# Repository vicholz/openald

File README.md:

# OpenALD v1.0

**OpenALD** is an open, rechargeable pocket FM radio: an ATmega328PB + RDA5807M (RRD-102 module) board that runs from one
18650 cell, charges and programs over a centred USB-C port, and lives in a 3D-printed 43 × 92 × 33.4 mm case. The repo also
holds an **Adafruit Feather RP2040 variant** built from off-the-shelf boards, and a **6-slot USB-C PD charging dock** that
fits both radios. Everything is KiCad 9 + OpenSCAD, generated by Python scripts.

> **Status: designed, CAD- and datasheet-checked, NOT built and NOT hardware-validated.** ERC/DRC, the JLC placement
> check and the 3D case-fit checks pass, but no board has been built, powered or programmed. The only firmware is the Feather variant's Arduino sketch, which compiles but has never run on hardware; the single board still has none.
> Treat the first build of each part as a prototype (see the bring-up checklist in [HANDOFF.md](HANDOFF.md#8-hardware-bring-up-test-checklist)).

**Picking this up later (person or AI)? Start with [HANDOFF.md](HANDOFF.md)**: full design history, decisions, hard
constraints, open TODOs, test checklist and exact regeneration commands.

| Folder | What it is | Status |
|---|---|---|
| [`radio_single_board/`](radio_single_board/README.md) | **OpenALD v1.0** single-board radio: ATmega328PB + RDA5807M, CH340K USB-C programming, TP4056 ~900 mA charging with DW01A/FS8205A protection and reverse-cell protection, thumbwheel (press = battery check), slide switch, centred vertical 3-LED level bar. 38 × 87 mm 2-layer PCB; case 43 × 92 × 33.4 mm | Designed; ERC/DRC/JLC-CPL/case fit pass; not built |
| [`charging_dock/`](charging_dock/README.md) | **OpenALD Dock v1.0**: 6 radios (2 × 3, 1 in apart) stand USB-C-down in 2 in pockets; one rear USB-C PD input (≥ 45 W charger, 15 V or 20 V); HUSB238 + 2 × SY8205 bucks + SY6280 limit per slot. 192 × 112 × 62.5 mm | Designed; ERC/DRC/JLC-CPL/fit pass; not built |
| [`radio_adafruit_feather_rp2040/`](radio_adafruit_feather_rp2040/README.md) | **OpenALD Feather RP2040 v1.0**: Feather RP2040 + RDA5807M breakout with jack + 18650 holder in a printed frame; **no PCB**: SIQ-02FVS3 wheel glued into a frame cradle, screwless SS-12F16 switch pressed into a groove in the case wall, frame clamped between the case halves, all hand-wired; same dock footprint at the base | Designed; fit check pass; FM-module dimensions are estimates; not built |

Dock ↔ radio mechanical contract: [`charging_dock/DOCK_INTERFACE.md`](charging_dock/DOCK_INTERFACE.md).

## Quick links
* Single-board radio: [Gerbers](radio_single_board/fab/openald-gerbers-jlcpcb.zip) · [JLC BOM](radio_single_board/fab/openald-BOM-jlcpcb.csv) · [JLC CPL](radio_single_board/fab/openald-CPL-jlcpcb.csv) · [human BOM](radio_single_board/fab/openald-BOM-human.csv) · [minimal (4-part) assembly set](radio_single_board/fab/minimal/) · [PCBWay BOM](radio_single_board/fab/openald-BOM-pcbway.xlsx) · [NextPCB BOM](radio_single_board/fab/openald-BOM-nextpcb.xls) · [schematic PDF](radio_single_board/docs/openald-schematic.pdf) · [case STLs](radio_single_board/case/)
* Dock: [Gerbers](charging_dock/fab/openald-dock-gerbers-jlcpcb.zip) · [JLC BOM](charging_dock/fab/openald-dock-BOM-jlcpcb.csv) · [JLC CPL](charging_dock/fab/openald-dock-CPL-jlcpcb.csv) · [human BOM](charging_dock/fab/openald-dock-BOM-human.csv) · [schematic PDF](charging_dock/docs/openald-dock-schematic.pdf) · [case STLs](charging_dock/case/)
* Feather variant: [BOM](radio_adafruit_feather_rp2040/docs/BOM.md) · [pin map](radio_adafruit_feather_rp2040/docs/pin_map.md) · [wiring diagram](radio_adafruit_feather_rp2040/docs/wiring_diagram.png) · [wiring schematic PDF](radio_adafruit_feather_rp2040/docs/wiring_schematic/openald-feather-wiring.pdf) · [firmware](radio_adafruit_feather_rp2040/firmware/) · [firmware notes](radio_adafruit_feather_rp2040/docs/firmware_notes.md) · [case STLs](radio_adafruit_feather_rp2040/case/stl/)
* Ready-made zip packages per subproject: GitHub Release **v1.0** assets (or build them with `tools/make_packages.sh`).

## How to order (JLCPCB)
**Board settings for every board:** 2 layers, **1.6 mm** FR-4, **1 oz** copper, any colour, HASL lead-free (or ENIG),
**PCB Assembly: Economic, top side**. Upload the gerber zip from the subproject's `fab/`, then the `*-BOM-jlcpcb.csv` and
`*-CPL-jlcpcb.csv`. Use the centroid `.csv` or `.pos` only if a site asks for those formats.

* **Check every part's rotation in JLC's placement preview before paying.** The CPLs already contain per-part EasyEDA
  origin/rotation corrections (`JLC_CORR`, verified by `jlc_cpl_fit.py --check`), so the preview should be right; JLC
  engineers sometimes re-rotate by hand.
* Single-board radio: U4 (RRD-102 module), BT1 (18650 holder) and J3 (ISP pads, do not fit) are hand-solder/DNP.
  SW1 (SK-12E12-G5) is THT: choose Standard PCBA to have JLC fit it, or deselect it and hand-solder (5 joints).
  If the ATmega328PB (C132230) is low/out of stock, use **ATmega328P-AU (C14877)**, a drop-in (pick the 328P variant in MiniCore).
* **Minimal assembly option** (you have hot air/hotplate): upload the same gerbers with
  `radio_single_board/fab/minimal/openald-BOM-jlcpcb-minimal.csv` + `openald-CPL-jlcpcb-minimal.csv`. JLC places only
  J1 (USB-C), U1 (TP4056), U3 (ATmega328PB) and U7 (CH340K); buy the rest from LCSC with
  `fab/minimal/openald-LCSC-order-handsolder.csv` (5 boards + labelled spares). Order a separate **frameless** stencil
  (~$3) if you want one for hand paste.
* Dock: the six vertical USB-C plugs J2–J7 (HX TYPE C-M 16P V-SMT, **LCSC C55200592, low stock**) are hand-soldered; buy 7.
* Other vendors (PCBWay/NextPCB) have filled BOM templates, but **the CPL/placement files contain JLC-specific
  corrections**; generate a clean placement file before using another assembler (see HANDOFF §6).
* Cost figures in the docs are **estimates from published price tables (2026-11-10/11)**, not quotes.

## How to regenerate / check
Tested with: **KiCad 9.0.2** (`kicad-cli` + `pcbnew` Python module), **OpenSCAD 2021.01**, **Python 3.13**,
Freerouting (2026-10 build, Java 21+; run with OpenJDK 25) for re-routing only. Python packages: see
[`requirements.txt`](requirements.txt) (`pcbnew` comes with KiCad, not pip).

```bash
pip install -r requirements.txt
tools/fetch_kicad3d.sh && export KICAD9_3DMODEL_DIR=$PWD/tools/kicad3d   # stock KiCad STEP models for the fit checks
tools/check_all.sh            # ERC + DRC + JLC CPL check for all three boards (non-destructive, ~10 s)
tools/check_all.sh --case     # + rebuild cases and run the 3D fit checks (slow; rewrites STLs/previews)
```
Per subproject (details and expected results in [HANDOFF.md §7](HANDOFF.md#7-regeneration-and-checks)):
* `radio_single_board/scripts/run_all_pcb.sh` (full schematic → board → **re-route** → DRC; needs Freerouting),
  `python3 scripts/make_fab.py` / `--minimal`, `python3 scripts/make_vendor_boms.py`, `scripts/build_case.sh`.
* `charging_dock/scripts/run_all_pcb.sh`, `python3 scripts/make_fab.py`, `scripts/build_case.sh`.
* `radio_adafruit_feather_rp2040/make_all.sh` (everything) or `case/build_case.sh` (case only).
* `OPENALD_OFFLINE=1` makes `make_fab.py` reuse the saved `fab/lcsc_lookup.json` prices instead of querying JLC's parts API.
* `FREEROUTING=/path/freerouting.jar` and `JAVA=/path/java` override the router location (default `tools/freerouting.jar`, not in git).
* `EASYEDA_CACHE` overrides the EasyEDA footprint cache used by `jlc_cpl_fit.py` (default: the committed `tools/easyeda/`).

## Directory map
```
README.md            this file            HANDOFF.md        full resume / handoff document
LICENSE              CC0 1.0 Universal    requirements.txt  Python deps
tools/               check_all.sh, fetch_kicad3d.sh, make_packages.sh, easyeda/ (EasyEDA footprint cache for jlc_cpl_fit)
radio_single_board/  kicad/ fab/ (gerbers, JLC BOM/CPL, centroid, .pos, vendor BOMs, minimal/) case/ previews/ docs/ scripts/
charging_dock/       kicad/ fab/ case/ (STLs, floor_pads/) previews/ docs/ scripts/ DOCK_INTERFACE.md
radio_adafruit_feather_rp2040/  case/ (stl/) previews/ docs/ scripts/ ref/ (Adafruit Eagle board, CC BY-SA) archive/ (retired PCB) make_all.sh
```

## License
Released into the public domain under **CC0 1.0 Universal** ([LICENSE](LICENSE)): hardware designs, scripts and docs.
Third-party reference files keep their own licenses (notably the Adafruit Feather RP2040 Eagle file in
`radio_adafruit_feather_rp2040/ref/`, CC BY-SA); see [HANDOFF.md §11](HANDOFF.md#11-license-and-third-party-files).

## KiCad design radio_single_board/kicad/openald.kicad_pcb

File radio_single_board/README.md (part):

# OpenALD: PCB, assembly files and 3D-printed case (v1.0)

OpenALD is an ATmega328PB + RDA5807M (RRD-102 module) FM radio, **programmable over its USB-C port** (CH340K USB-serial, Arduino IDE / MiniCore). It runs from one 18650 cell (reverse-polarity protected), charges over USB-C (TP4056 + DW01A/FS8205A protection) and uses an XC6206 3.3 V LDO. Controls are a thumbwheel encoder with push for volume and tuning (**press the wheel = battery check**; there is no separate battery-check button any more), and a slide power switch that sticks out of the case. A **3-LED battery-level bar** runs as a **vertical column centred across the front face** near the jack end (so it stays well above the rim when the radio stands USB-C-down in the OpenALD Dock), and the TP4056 red/green charge LEDs sit next to the USB-C. The headphone cable acts as the antenna. The board silkscreen reads **OpenALD v1.0**.

> **Note:** I couldn't open the attached spec file on the build machine. This design follows the written summary of the spec instead, so compare it against your original.

> **OpenALD v1.0 is untested hardware.** This release is the former FM radio rev 4.3 design, renamed and reset to v1.0, with no electrical changes. Since then (all still v1.0): the level bar moved to a vertical column near the jack end for the charging dock, and on 2026-11-11 the separate battery-check button SW2 was removed (the wheel press does its job through a small P-FET, Q4) and the bar was centred across the board and moved up (see "Wheel press replaces the battery-check button"). On 2026-11-12 the USB-C receptacle J1 moved 0.9 mm toward the board edge and the case got the Feather's straight cable-plug recess plus assembly notches (see "USB-C 0.9 mm out to the case face"). It passes ERC, DRC and the 3D case-fit check. Pre-release rev 4.2 had two full datasheet reviews, and rev 4.3 (which only changed the charge-current resistor) had its own independent review (see "Pre-release history" below). No board has been built or programmed yet. Build one or two first.

The hardware in this v1.0 package is the ~900 mA charge-current design (R3 = 1.2k, TP4056 PROG). Charge time for a 3000 mAh 18650 is about 3.7 h if the chip holds 900 mA through the CC phase, likely closer to ~4 h in the closed case if the TP4056 thermally throttles. Use a **≥ 1 A charger**. A laptop USB 2.0 port is only rated 500 mA. If you need to charge from a laptop USB-A port, change **R3 to 2.4k (C22940, Basic) for ~460 mA**. See the pre-release rev 4.3 notes for the thermal estimate, USB source details, and the first-board cell-temperature check.

## Board at a glance
| | |
|---|---|
| Size | **38.0 x 87.0 mm**, 1.6 mm FR-4, 2 layers, 1 oz, 3 mm corner radius |
| Mounting | 4x M2 holes (2.2 mm) at (3.2, 3.2), (34.8, 3.2), (3.2, 83.8), (34.8, 83.8) mm from the top-left corner |
| Top side | All SMT parts (including the 3 level-bar LEDs), plus the power switch (THT) and the hand-soldered RRD-102 module |
| Bottom side | MPD BH-18650-PC holder only (THT, hand-soldered) |
| Copper | GND pour on both layers, stitched with 102 GND vias (rev 4.2: 89 stitching vias on two offset 2.5 mm grids, 3 thermal vias in the TP4056 pad, plus routed GND vias). Power nets are 0.5 mm, signals 0.25 mm (0.15 mm minimum at the TQFP/ESSOP pins). Vias are 0.6/0.3 mm (0.8/0.4 mm on power). The autorouter ran with a 0.45 mm edge keep-out |
| ERC | **0 errors**, 2 accepted warnings (`fab/erc_report.txt`): pin_to_pin on U3 pins 3/6 (PE0 tied to GND, PE1 tied to +3V3 for ATmega328P-AU drop-in). This is intentional |
| DRC | **0 errors, 0 unconnected pads, 0 schematic-parity issues** (re-run after the 2026-11-11 wheel-press / centred-bar update). 62 cosmetic silkscreen warnings are waived: 8 silk_edge_clearance (the jack, wheel and switch overhang the edge on purpose), 24 silk_over_copper (reference text over pads/vias) and 30 silk_overlap. Min track 0.187 mm (rule 0.15 mm), tracks/vias ≥ 0.75 mm from the edge (`fab/drc_report.txt`) |

## How charging is shown (power switch off or on)
The power switch cuts VSYS. In rev 4 the MCU also runs from USB with the switch off (see "Power path"), so firmware can show the charging animation on its own while USB is plugged in (optional). The rev 3 options still work:
1. **Always, with no MCU needed:** the TP4056's own LEDs, **D3 red = charging and D4 green = full**, light from USB power. They shine through their own two light tunnels just left of the USB-C. This works with the switch off.
2. **With the switch off, hold the wheel pressed in:** the wheel's push switch turns on P-FET Q4, which powers the MCU from the battery (through D10, and VSYS through D2) for as long as the wheel is held in. While held, the MCU reads nCHRG and shows the charging animation or the level on the bar. Releasing the wheel powers it off again.
3. **With the switch on:** a short press of the wheel any time shows the level on the bar, or the charging animation if USB is charging. Plugging USB in while the radio is on also shows the charging animation once for 3 s.

Rev 4 powers the MCU from USB through its **own** LDO (U6) instead of feeding VBUS into VSYS. That way the FM module and the battery divider stay off. Note that while USB is powering the MCU with the switch off, BAT_ADC reads about 0 V, so the cell voltage isn't measurable then. For the level while charging, hold the wheel in (VSYS then sees the cell through Q4 and D2) or switch on.

## Files
```
kicad/                     KiCad 9 project (open openald.kicad_pro)
  openald.kicad_sch       schematic (PDF in docs/openald-schematic.pdf)
  openald.kicad_pcb       routed board
  openald.pretty/         custom footprints: RRD-102 module, Mitsumi SIQ-02FVS3, HRO SK-12E12-G5 switch (U3/U7/U8 use stock KiCad footprints)
  openald.kicad_sym       custom symbols;  openald.3dshapes/  simple 3D models for previews and the fit check
fab/
  openald-gerbers-jlcpcb.zip   Gerbers + Excellon drill files (upload this)
  openald-BOM-jlcpcb.csv       JLC assembly BOM (Comment, Designator, Footprint, LCSC Part #)
  openald-CPL-jlcpcb.csv       JLC pick-and-place (Designator, Mid X, Mid Y, Layer, Rotation), corrected for EasyEDA origins
  openald-centroid.csv         standard centroid / XY file (Designator, Comment, Footprint, Mid X, Mid Y, Rotation, Layer); same positions as the JLC CPL
  openald.pos                  KiCad ASCII position file (mm); same corrected positions as the centroid/CPL, plus hand-soldered U4 and BT1
  jlc_cpl_fit.json              per-part fit of the EasyEDA footprints (offsets, rotations, pad match)
  openald-BOM-human.csv        full BOM with MPNs, qty, live LCSC stock and price, links, plus hand-solder and off-board parts
  openald-BOM-pcbway.xlsx      PCBWay SMT assembly BOM (official template filled; qty per board; title says 5PCS)
  openald-BOM-nextpcb.xls      NextPCB assembly BOM (official template filled; qty per board)
  minimal/                      JLC files for a 4-part "hotplate" assembly only (see below)
    openald-BOM-jlcpcb-minimal.csv
    openald-CPL-jlcpcb-minimal.csv
    openald-centroid-minimal.csv
    openald-minimal.pos
    openald-LCSC-order-handsolder.csv   remaining LCSC parts for 5 boards, with labelled spares
    cost_estimate.txt
  erc_report.txt, drc_report.txt, lcsc_lookup.json, cost_summary.json
case/
  openald_case.scad       parametric OpenSCAD case (includes case_params.scad)
  case_params.scad         AUTO-GENERATED from the PCB by scripts/gen_case_params.py
  case_top.stl, case_bottom.stl   heat-set-insert version (default)
  nut_variant/             same case with M2 hex-nut pockets instead of inserts
  case_fit_report.txt      3D interference check of the assembled PCB against both halves and the LED tunnel walls
previews/                  pcb_top.png, pcb_bottom.png, pcb_closeup_led_bar.png, pcb_closeup_reverse_polarity.png,
                           pcb_closeup_polarity_marks_bottom.png (rev 4.2), schematic-1.png, case_closed.png, case_*.png,
                           closeup_led_bar.png, closeup_front_usb_leds.png, cutaway_led_tunnels.png (section through the bar),
                           closeup_power_switch.png, closeup_usb_c.png, closeup_thumbwheel.png, closeup_jack_end.png,
                           cpl_overlay_<REF>.png (EasyEDA/JLC footprint vs KiCad pads; rev 4 adds U3/U6/U7/U8, rev 4.2 Q2/Q3, 2026-11-11 Q4),
                           pcb_closeup_usb_serial.png
docs/openald-schematic.pdf
scripts/                   generator scripts. run_all_pcb.sh regenerates everything up to DRC,
                           make_fab.py the fab outputs (add --minimal for the hotplate assembly set),
                           make_vendor_boms.py the PCBWay/NextPCB BOMs (templates in scripts/templates/),
                           build_case.sh the case, its checks and the renders
```

## Ordering at JLCPCB (assembled)
1. Upload `fab/openald-gerbers-jlcpcb.zip`. Settings: 2 layers, 38x87 mm, 1.6 mm, any colour, HASL (lead-free) or ENIG.
2. Turn on **PCB Assembly**, top side.
3. Upload `openald-BOM-jlcpcb.csv` and `openald-CPL-jlcpcb.csv`. If a site asks for a centroid or XY file instead, use `openald-centroid.csv` (same positions, plus value and footprint columns). If it asks for a `.pos` or KiCad position file, use `openald.pos`. U4, BT1 and J3 have no JLC placement, so they show as "not selected". Leave them that way, because you hand-solder them (J3 is not fitted).
4. **SW1 (SK-12E12-G5) is a through-hole part.** If you want JLC to solder it, pick **Standard PCBA**, which adds JLC's THT soldering fee. To keep the cheaper Economic SMT-only service, deselect SW1 and hand-solder it, which is 5 easy joints. Buy it from LCSC (C136720) in that case.
5. **Check every part's orientation in JLC's placement preview** before paying. The CPL has per-part corrections fitted against the EasyEDA footprints JLC uses (see "What changed in rev 3.1"), so the preview should show every part on its pads. The pin-1 and polarity marks to watch are U1, U2, Q1, Q2, Q3, Q4 (SOT-23 FETs), U3 (TQFP-32 pin-1 dot), U5, U6, U7 (CH340K), U8 (USBLC6), D2, D7, D8, D9, D10 and the LEDs D1, D3, D4, D5, D6 (cathode = pad 1, on the left for the bar LEDs). Also check that J1, J2, SW1 and SW3 face the board edge.
6. Parts cost about **$7.32 per board** for the JLC-placed parts (LCSC qty-10 prices from the cached 2026-11-10 lookup, including SW1). The 2026-11-11 wheel-press update removed SW2 (Panasonic EVQ-P7A01P, C79167, Extended, $0.187) and added Q4 (AO3401A, C15127, Basic, $0.081) + R25 (1M, C22935, Basic, $0.002): **−$0.10 per board** vs the previous $7.43, and **one fewer extended part type**. Rev 4.1 was $7.28, **+$0.42 over rev 3.1 ($6.86)**: the ATmega328PB costs more than the ATtiny84A, plus the CH340K ($0.55), the USBLC6 ($0.16), the second XC6206 ($0.13), 3 more B5819W and some passives. On top of that come the PCB, the assembly fee, and the Economic-PCBA extended-part loading fee (~$3.07 per part type per order). There are **11 extended part types**, but **C16581 (TP4056) is a JLC *Preferred* extended part, which has no loading fee**, so **10 types are charged**: C12624, C132230, C136720, C165948, C2830320, C2925423, C351410, C7519, C95562, C968586. That's about **$31 per order** (was ~$34 with SW2; about $28 if you deselect the through-hole SW1 and hand-solder it). Hand-solder and off-board parts add roughly $10 per unit: module ~$1-2, holder ~$3, cell ~$5, screws and inserts.
7. Stock checked 2026-11-10 (re-checked for rev 4.3): **ATmega328PB-AU (C132230) still only 735** (was 2,168 earlier today), R3 1.2k (C22765) 2,137,483 (Basic), AO3401A (C15127) 1,635,833, AO3400A (C20917) 990,950, 1M (C22935) 4,069,811. Earlier check (fallback ATmega328P-AU C14877: 22,013, same footprint and CPL), **CH340K (C968586) 33,016** (CH340N C2977777: 48,107 and CH340C C84681: 97,260 exist, but they are different packages and would need a footprint change), USBLC6-2SC6 (C7519) 28,286, SIQ-02FVS3 1,298, PJ-320D-4A 1,522, SK-12E12-G5 15,527 (EVQ-P7A01P no longer used). Re-check stock before ordering.

## BOM files for PCBWay and NextPCB
`fab/openald-BOM-pcbway.xlsx` and `fab/openald-BOM-nextpcb.xls` are the official vendor templates, filled from the v1.0 human BOM. Quantities are **per board** (75 placements, 37 line items). The PCBWay title says **5PCS** to match a 5-board order; NextPCB has no order-qty field — set the board count on their quote form. U4, BT1 and J3 are marked **DNS** (PCBWay) / **DNP** (NextPCB) so the assembler will not fit them: hand-solder U4 and BT1 yourself, and do not fit a header on J3. SW1 is listed as through-hole (PCBWay Type `thru-hole`). Off-board items (the 18650 cell, M2 screws and inserts) are not in these files; they stay in `openald-BOM-human.csv`. Manufacturer is filled only when the project data names one; most passives, the LEDs, the Schottkys, the beads, U4 and J3 leave that column blank. If you are soldering the boards yourself, buy a few extra 0603 passives and LEDs — quantities were not inflated for spares. Regenerate with `scripts/make_vendor_boms.py`.

## Minimal JLC assembly (hotplate parts only)
If you have a hot-air station and want JLC to place only the parts that are painful by hand, use the files in `fab/minimal/`. Upload the same Gerbers (`fab/openald-gerbers-jlcpcb.zip`), but use:

- `fab/minimal/openald-BOM-jlcpcb-minimal.csv`
- `fab/minimal/openald-CPL-jlcpcb-minimal.csv`

(or the matching centroid / `.pos` if the site asks for those). Regenerated with `python3 scripts/make_fab.py --minimal`. Positions use the same `JLC_CORR` EasyEDA origin/rotation fixes as the full CPL; `jlc_cpl_fit.py --check` and a pad-fit of this 4-row CPL both pass.

**JLC places these four parts (all top side):**

| Ref | Part | Why it is in the minimal set |
|---|---|---|
| J1 | HRO TYPE-C-31-M-12 mid-mount USB-C (C165948) | Mid-mount body sits in board-edge slots; hard to align and easy to melt with an iron or hot air |
| U1 | TP4056 ESOP-8 (C16581) | Exposed pad under the package; needs reflow or a hotplate to solder reliably |
| U3 | ATmega328PB-AU TQFP-32, 0.8 mm pitch (C132230) | No exposed pad, so hot air *can* do it, but 0.8 mm pitch is easy to bridge; factory placement is much more reliable |
| U7 | CH340K ESSOP-10 (C968586) | Exposed pad under the package; same as U1 |

**Looked at, but left off (your hot-air station is enough):** U2 (DW01A, SOT-23-6), Q1 (FS8205A, SOT-23-6 in this design — not TSSOP-8), U8 (USBLC6-2SC6, SOT-23-6), Q2/Q3/Q4 (SOT-23) and U5/U6 (SOT-23-3). All of those have side-only pins and no bottom-only pad. U4, BT1 and J3 stay hand-soldered / unfitted as before.

**Estimated JLC cost for 5 boards (estimate only, not a live quote):** about **$36** before shipping, tax or tariff, using the published Economic PCBA table (setup $8.18, stencil $1.53, $3.07 feeder × 3 extended types, SMT joints, $0.45 confirm-placement) plus ~$2 for 5 bare boards and **$14.35** in parts (qty-1 prices: the 328PB is $1.86 each at qty 5). The TP4056 is a Preferred extended part, so it has no feeder fee. The other three are Extended. Details are in `fab/minimal/cost_estimate.txt`. JLC keeps the Economic stencil; it is not shipped. If you want a stencil for the remaining SMT, order a separate frameless one from JLC (~$3) for hand paste + hot air.

**Parts you buy and solder yourself:** `fab/minimal/openald-LCSC-order-handsolder.csv` is an LCSC order list for everything else on the board that has an LCSC number. Quantities are **5 boards plus labelled spares** (+10 on 0603 passives, +3 on 0603 LEDs and SOD-123 diodes, +2 on 0805/1206 caps, +1 on SOT-23s and unique mechanicals). The Mitsumi wheel (SW3) spare is marked optional because that part is about $3. You also still need the RRD-102 module (U4), the MPD BH-18650-PC holder (BT1), an 18650 cell, and the M2 screws and inserts — those are not in the LCSC list; see the human BOM.

## Hand assembly after JLC delivers the board
| Ref | Part | Notes |
|---|---|---|
| U4 | RRD-102V2.0 RDA5807M module (11x11 mm, 2.0 mm pitch) | Solder flat on its pads, chip side up. Check the L/R pads (see caveats). |
| SW1 | HRO SK-12E12-G5, if JLC didn't fit it | Seat it fully, with the knob pointing off the right edge, and solder the 3 pins and 2 tabs. |
| BT1 | MPD BH-18650-PC holder, bottom side | Polarity is printed on the bottom silk: large "+" / "BAT+" beside the holder at the USB-C end, "−" / "BAT−" at the jack end. **The holder itself can be soldered either way round** (its two pins are symmetric), so fit it with its moulded **+ end (flat contact) on the square pad at the USB-C end** and the spring (−) at the jack end, then check with a meter before inserting a cell. A reversed cell is now harmless (rev 4.2), but the radio won't run until it is turned round. |
| J3 | 2x3 ISP pads | Do not fit a header (the case won't close over it). Use a 2x3 pogo clip/adapter once, to burn the bootloader. |

## Programming
**Once per board, burn the bootloader over ISP:**
1. Arduino IDE -> Boards Manager: install **MiniCore** (MCUdude; board-manager URL `https://mcudude.github.io/MiniCore/package_MCUdude_MiniCore_index.json`).
2. Tools: Board **ATmega328**, Variant **328PB** (or **328P / 328PA** if you fitted the C14877 fallback), Clock **Internal 8 MHz**, BOD **2.7 V** (or 1.8 V), EEPROM retained, Bootloader **Yes (UART0)**, Baud rate: the default (38400 for 8 MHz internal is the safest; 115200 is often unreliable on the RC oscillator).
3. Connect a **3.3 V** ISP programmer (USBasp set to 3.3 V, or an Arduino-as-ISP with a level-safe setup) to the J3 pogo pads (standard 6-pin AVR ISP, pin 1 = MISO). Either let the programmer supply 3.3 V on VCC, or set it to "no power" and power the board from USB-C with the switch off. **Never put 5 V on VCC.** It would back-feed the RDA5807M through the I2C lines and push 5 V into U6's output.
4. Tools -> **Burn Bootloader**. This sets the fuses (internal 8 MHz) and writes Optiboot.

**After that, upload over USB-C:** plug in USB-C (the power switch can stay **off**, and the radio stays unpowered), choose the CH340 serial port, and click **Upload** with the same MiniCore settings. DTR# auto-resets the MCU into Optiboot. Windows needs the WCH CH340/CH341 driver (CH341SER), and macOS 11+ / Linux include one.

**Power switch:** slide toward the headphone-jack end = **ON**; toward the USB-C end = OFF. On an SPDT slide switch, the slider joins the common pin (2) to the outer pin on the knob's side, so the knob at the pin-3 end connects 2-3. Pin 2 is VBAT and pin 3 is VSYS, so 2-3 = ON. Pin 3 is the pin nearest the jack end. Check with a meter before closing the case.

## ATmega328PB pin map (TQFP-32) - MiniCore Arduino pin names
| Pin | Port | Arduino | Net | Function |
|---|---|---|---|---|
| 1 | PD3 / INT1 | D3 | ENC_B | encoder B (internal pull-up) |
| 2 | PD4 | D4 | - | **spare** since 2026-11-11 (was ENC_SW). The wheel press is now read on PC1 / BTN_SENSE (pin 24) |
| 3 | PE0 | (D23) | GND | tied to GND for ATmega328P drop-in. **Leave as input, no pull-up** |
| 4 | VCC | | +3V3 | MCU rail (U6), 100 nF C7 |
| 5 | GND | | GND | |
| 6 | PE1 | (D24) | +3V3 | tied to +3V3 for ATmega328P drop-in. **Leave as input, no pull-up** |
| 7, 8 | PB6, PB7 | | - | no crystal (internal 8 MHz RC); spare |
| 9 | PD5 / OC0B | D5 | LVL1 | level LED 1 (D1, bottom of the column / lowest), 1k, active high, PWM |
| 10 | PD6 / OC0A | D6 | LVL2 | level LED 2 (D5, middle), 1k, active high, PWM |
| 11, 12 | PD7, PB0 | D7, D8 | - | spare |
| 13 | PB1 / OC1A | D9 | LVL3 | level LED 3 (D6, top of the column, nearest the jack / full), 1k, active high, PWM |
| 14 | PB2 | D10 | - | spare |
| 15 | PB3 / MOSI | D11 | MOSI | ISP only (J3) |
| 16 | PB4 / MISO | D12 | MISO | ISP only (J3) |
| 17 | PB5 / SCK | D13 | SCK | ISP only (J3) |
| 18 | AVCC | | +3V3 | 100 nF C13 |
| 19 | ADC6 | A6 | - | spare (analog only) |
| 20 | AREF | | AREF | 100 nF C14 (use the internal 1.1 V reference) |
| 21 | GND | | GND | |
| 22 | ADC7 | A7 | - | spare (analog only) |
| 23 | PC0 / ADC0 | A0 | BAT_ADC | battery voltage (VSYS), 47k/12k divider + 100 nF (rev 4.1) |
| 24 | PC1 / ADC1 | A1 | BTN_SENSE | **wheel press** (SW3 S → Q4 → VBTN → 4.7k/10k divider; **high = pressed**, no pull-up: `pinMode(A1, INPUT)`; can also be read as ADC1, threshold ≈ 1.3 V). Wakes the MCU via PCINT9 |
| 25 | PC2 | A2 | CHRG_SENSE | TP4056 nCHRG through Schottky D7; enable the internal pull-up; **low = charging** |
| 26 | PC3 | A3 | - | spare |
| 27 | PC4 / SDA0 | A4 (SDA) | SDA | I2C to RDA5807M (1k series R16, 4.7k pull-up R14 to +3V3R) |
| 28 | PC5 / SCL0 | A5 (SCL) | SCL | I2C (1k series R17, 4.7k pull-up R15 to +3V3R) |
| 29 | PC6 / RESET | | nRESET | 10k pull-up R10, ISP RESET, DTR# auto-reset via 100 nF C19 |
| 30 | PD0 / RXD0 | D0 | MCU_RX | from CH340K TXD (10k pull-up R19) |
| 31 | PD1 / TXD0 | D1 | MCU_TX | to CH340K RXD through 1k R20 |
| 32 | PD2 / INT0 | D2 | ENC_A | encoder A (internal pull-up) |

**Pin budget:** 16 I/O are used, and PB0, PB2, PB6, PB7, PC3, PD4, PD7 and ADC6/7 are spare (not broken out). nSTDBY (full) isn't read: "full" is the same as "USB present, not charging, cell ≥ 4.10 V". The green D4 shows "full" in hardware.

Firmware notes: use the hardware TWI (`Wire`). The RDA5807M uses I2C address 0x10 for sequential access and 0x11 for random access. Before talking to the radio, check that it is powered (switch on), because with only USB present the +3V3R rail and the I2C pull-ups are off. Measure BAT_ADC against the internal 1.1 V reference (`analogReference(INTERNAL)`): V_sys = ADC/1023 x 1.1 x 59/12 (rev 4.1 divider 47k/12k). With these values 4.2 V reads about 0.85 V (ADC ≈ 795 with a nominal 1.1 V reference); calibrate the reference once per board, since it is only guaranteed 1.0-1.2 V. **Don't call `Wire.begin()` while the radio rail is off** (switch off): it enables the AVR's internal pull-ups on SDA/SCL, which would trickle ~80 µA per line into the unpowered RDA5807M; start `Wire` only after V_sys > 3 V, and call `Wire.end()` plus `pinMode(SDA/SCL, INPUT)` before the radio loses power. Keep BOD at 2.7 V (8 MHz needs ≥ ~2.4 V). If you only need it for programming, call `Serial.end()` and leave PD1 as an input when you don't need serial.

### Firmware spec: thumbwheel encoder (SIQ-02FVS3)

Paper-verified against the Mitsumi SIQ series datasheet ([LCSC copy of the official PDF](https://datasheet.lcsc.com/datasheet/pdf/7bff72617d5a3503f5ed21ab02a77dea.pdf?productCode=C2925423)). Nothing here has been tested on hardware.

The part is a 15-detent quadrature encoder plus a momentary slide/push switch. Terminals A and B are the encoder contacts, S is the push switch, and C is the common for all three (see the datasheet "CIRCUIT" diagram). On this board C is tied to GND, A goes to **D2 / PD2 / INT0** and B to **D3 / PD3 / INT1**. **The push switch S no longer goes to an MCU pin** (2026-11-11, it replaced the battery-check button): S drives the gate of P-FET **Q4** (AO3401A) with a 1 MΩ pull-up R25 to VBAT. Pressing the wheel pulls the gate to GND, Q4 switches VBAT onto VBTN, and the MCU sees the press as **BTN_SENSE high on A1 / PC1** (4.7k/10k divider; no internal pull-up). The same path powers the MCU when the power switch is off, so holding the wheel in is the off-state battery check. The S contact carries only ~4 µA (VBAT / 1 MΩ). A and B have no external pull-ups, no RC filters and no ESD diodes: enable the ATmega328PB internal pull-ups (20–50 kΩ, DS40001906) in `setup()` with `INPUT_PULLUP`. At 3.3 V that is about 66–165 µA per closed contact, under the 0.5 mA / 5 V DC rating. The datasheet does not specify a minimum wetting current or a bounce time.

The output is a 2-bit Gray-code quadrature waveform, **one full cycle (four valid state changes) per detent** (24° ±3°, 15 detents per turn). Clockwise, A leads B. At rest in a detent, A and/or B may already be low, so do **not** use INT0/INT1 low-level interrupts to wake from Power-down — the MCU would never stay asleep. Pin-change interrupts on PD2/PD3 (`PCINT18/19`, PCI2) for the turn and on PC1 (`PCINT9`, PCI1) for the press do wake from Power-down and Standby on any edge (BTN_SENSE idles low and goes high on a press). INT0/INT1 any-edge interrupts are fine while awake, but a 1 ms poll of the state table below also debounces, so a timer tick is the simplest approach. Count **one step per detent** (accumulate ±4 transitions), not one step per edge, or volume will jump four units per click.

**Wheel behaviour (v1.0, 2026-11-11):**

| Action | Power switch ON | Power switch OFF |
|---|---|---|
| Turn | volume | nothing (MCU unpowered, or on USB only) |
| **Short press** (released < 500 ms, no turn while pressed) | **battery check**: bar shows the level (or the charging animation) for 3 s | — |
| **Hold pressed** | after 500 ms with no turn: **seek** (next station) | **battery check while held**: the press itself powers the MCU; bar shows level / charging until release |
| Push and turn | tune (step the frequency); no battery check, no seek | — |

The switch-off case is detected at power-on: a power-on reset with BTN_SENSE already high means "wheel-powered" (see the battery-bar spec). There is no mute function on the wheel (there never was one); add one in firmware if you want it, e.g. double-press.

Example (MiniCore, board "ATmega328PB", 8 MHz internal). Call `encoder_setup()` from `setup()`, and `encoder_poll()` from a 1 ms tick or from `loop()` if you wait on `millis()`.

```cpp
// D2=ENC_A (PD2/INT0), D3=ENC_B (PD3/INT1), A1=BTN_SENSE (PC1): wheel press, HIGH = pressed
// (SW3 S -> Q4 gate; Q4 -> VBTN -> 4.7k/10k divider). Common C = GND. D4 (PD4) is spare.
const uint8_t PIN_A = 2, PIN_B = 3, PIN_SW = A1;
// prev<<2|curr -> +1 / -1 for a valid 1-step Gray-code move; 0 = bounce or invalid
static const int8_t ENC_TAB[16] = {
  0,-1,+1,0, +1,0,0,-1, -1,0,0,+1, 0,+1,-1,0
};
static uint8_t enc_prev;
static int8_t  enc_accum;
static int8_t  enc_step;        // +1 / -1 once per detent; consume in the main loop
static uint8_t sw_hist, sw_down, sw_turned;
static uint16_t sw_ms;
volatile uint8_t battery_check_request, seek_request;   // consumed by the main loop

void encoder_setup() {
  pinMode(PIN_A, INPUT_PULLUP);
  pinMode(PIN_B, INPUT_PULLUP);
  pinMode(PIN_SW, INPUT);         // external 10k pull-down R7; do NOT enable the pull-up
  enc_prev = (digitalRead(PIN_A) ? 2 : 0) | (digitalRead(PIN_B) ? 1 : 0);
}

void encoder_poll() {            // call every 1 ms
  uint8_t now = (digitalRead(PIN_A) ? 2 : 0) | (digitalRead(PIN_B) ? 1 : 0);
  enc_accum += ENC_TAB[(enc_prev << 2) | now];
  enc_prev = now;
  if (enc_accum >= 4)  { enc_step += 1; enc_accum = 0; }
  if (enc_accum <= -4) { enc_step -= 1; enc_accum = 0; }

  sw_hist = (sw_hist << 1) | (digitalRead(PIN_SW) ? 0 : 1);   // 0 = pressed (BTN_SENSE high)
  if (!sw_down && (sw_hist & 0x1F) == 0x00) { sw_down = 1; sw_ms = 0; sw_turned = 0; }  // 5 ms pressed
  if (sw_down) {
    if (enc_step) sw_turned = 1;            // push-and-turn = tune (main loop reads enc_step + sw_down)
    if (sw_ms < 60000) sw_ms++;
    if ((sw_hist & 0x1F) == 0x1F) {         // released
      if (sw_ms < 500 && !sw_turned) battery_check_request = 1;   // short press: show the bar for 3 s
      sw_down = 0;
    } else if (sw_ms == 500 && !sw_turned) {
      seek_request = 1;                     // long press: start seek
    }
  }
}
```

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
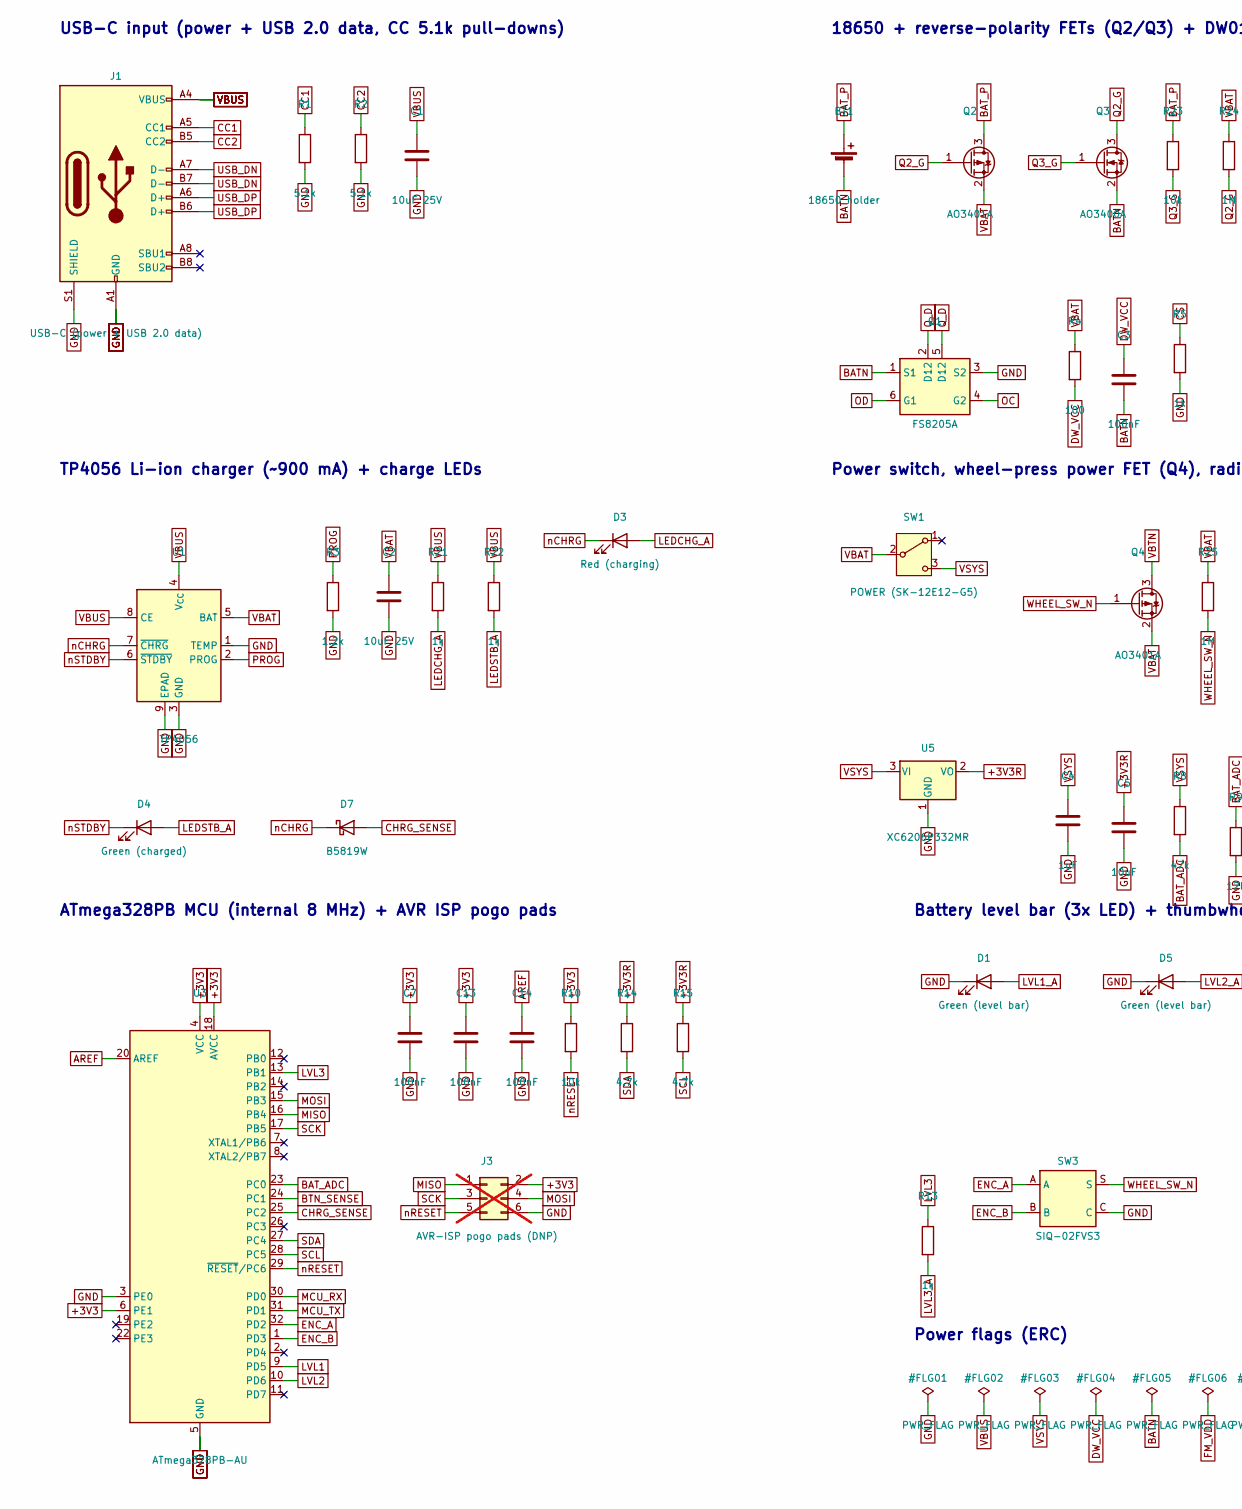
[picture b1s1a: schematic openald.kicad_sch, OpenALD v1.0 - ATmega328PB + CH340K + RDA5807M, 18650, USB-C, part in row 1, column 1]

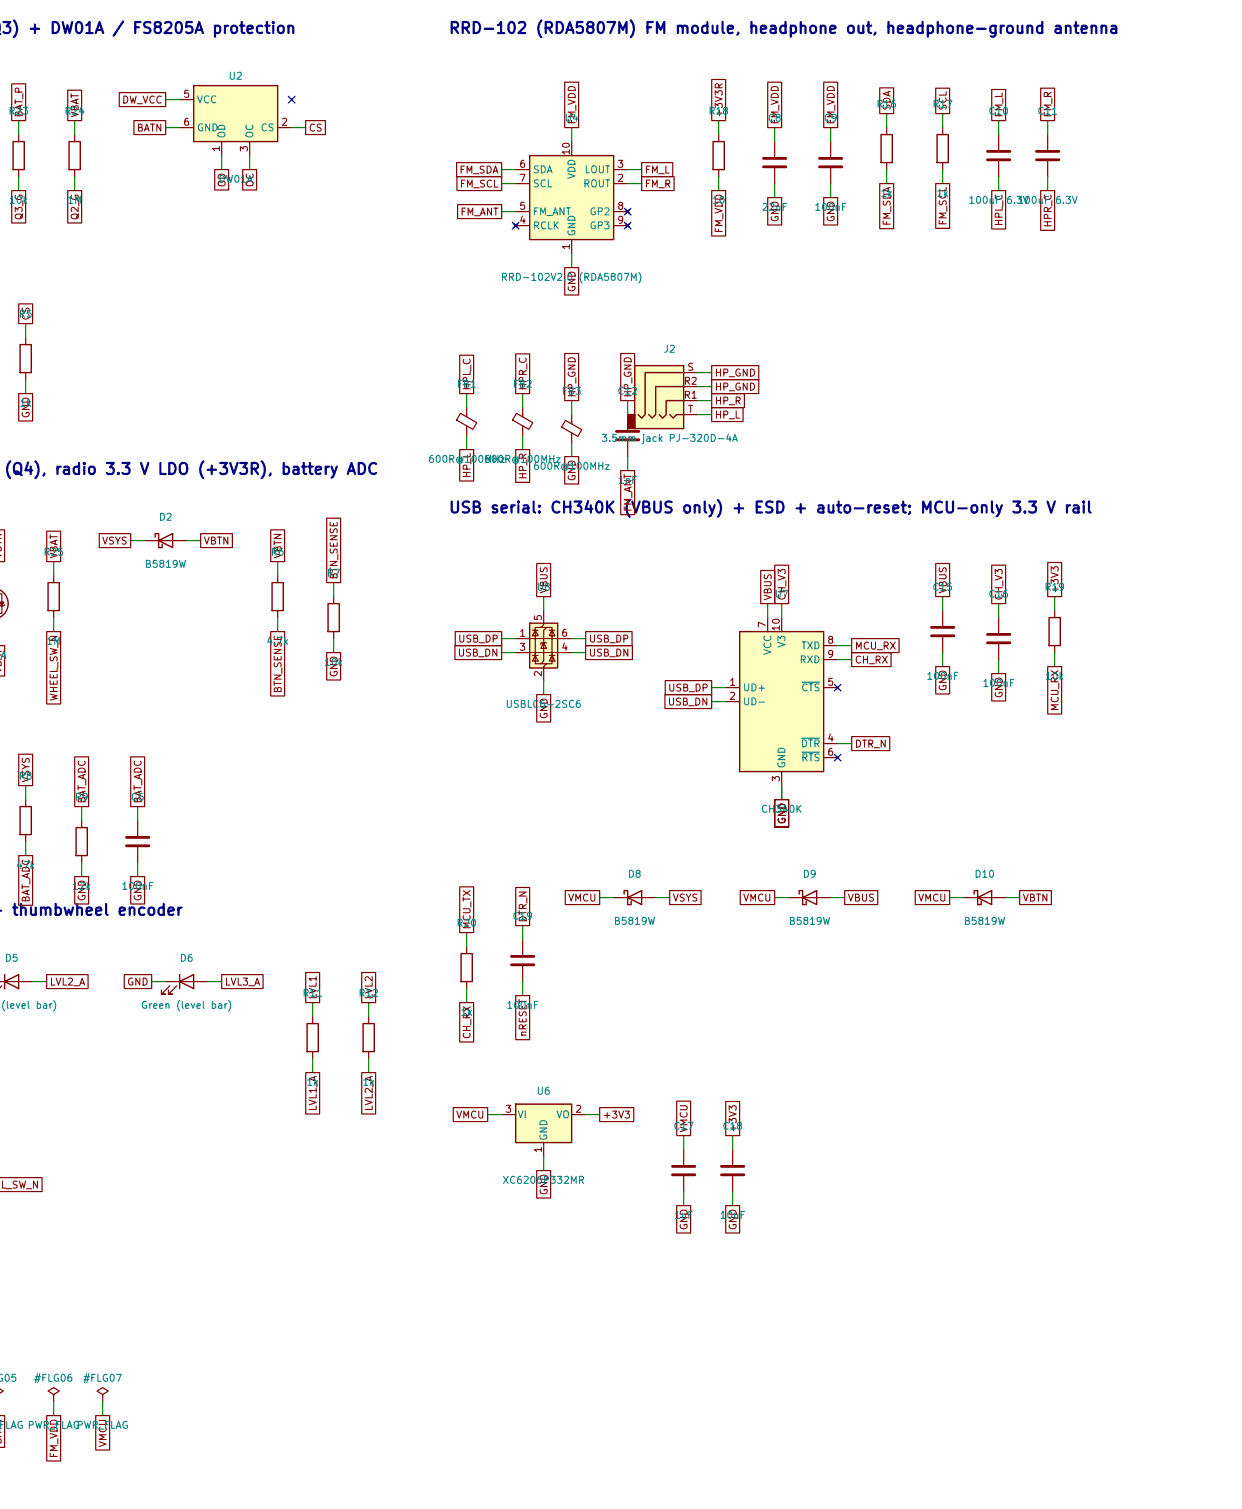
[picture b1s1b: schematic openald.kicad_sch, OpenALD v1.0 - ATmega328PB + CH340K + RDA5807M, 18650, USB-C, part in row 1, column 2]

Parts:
BT1: 18650 holder; BatteryHolder_MPD_BH-18650-PC; MPN MPD BH-18650-PC
C1, C2: 10uF 25V; C_0805_2012Metric; MPN CL21A106KAYNNNE; LCSC C15850
C3, C6, C7, C9, C13, C14, C15, C16, C19: 100nF; C_0603_1608Metric; MPN CC0603KRX7R9BB104; LCSC C14663
C4, C17: 1uF; C_0603_1608Metric; MPN CL10A105KB8NNNC; LCSC C15849
C5, C18: 10uF; C_0603_1608Metric; MPN CL10A106KP8NNNC; LCSC C19702
C8: 22uF; C_0805_2012Metric; MPN CL21A226MAQNNNE; LCSC C45783
C10, C11: 100uF 6.3V; C_1206_3216Metric; MPN CL31A107MQHNNNE; LCSC C15008
C12: 1nF; C_0603_1608Metric; MPN CL10B102KB8NNNC; LCSC C1588
D1, D5, D6: Green (level bar); LED_0603_1608Metric; MPN KT-0603G; LCSC C12624
D2, D7, D8, D9, D10: B5819W; D_SOD-123; MPN B5819W SL; LCSC C8598
D3: Red (charging); LED_0603_1608Metric; MPN KT-0603R; LCSC C2286
D4: Green (charged); LED_0603_1608Metric; MPN KT-0603G; LCSC C12624
FB1, FB2, FB3: 600R@100MHz; L_0603_1608Metric; MPN GZ1608D601TF; LCSC C1002
J1: USB-C (power + USB 2.0 data); USB_C_Receptacle_HRO_TYPE-C-31-M-12; MPN HRO TYPE-C-31-M-12; LCSC C165948
J2: 3.5mm jack PJ-320D-4A; Jack_3.5mm_KoreanHropartsElec_PJ-320D-4A_Horizontal; MPN HRO PJ-320D-4A; LCSC C95562
J3: AVR-ISP pogo pads (DNP); PinHeader_2x03_P2.54mm_Vertical; MPN 2x3 2.54mm header / pogo (DNP); not fitted
Q1: FS8205A; SOT-23-6; MPN FS8205A (TECH PUBLIC); LCSC C2830320
Q2, Q4: AO3401A; SOT-23; MPN AOS AO3401A; LCSC C15127
Q3: AO3400A; SOT-23; MPN AOS AO3400A; LCSC C20917
R1, R2: 5.1k; R_0603_1608Metric; MPN 0603WAF5101T5E; LCSC C23186
R3: 1.2k; R_0603_1608Metric; MPN 0603WAF1201T5E; LCSC C22765
R4: 100; R_0603_1608Metric; MPN 0603WAF1000T5E; LCSC C22775
R5, R11, R12, R13, R16, R17, R20, R21, R22: 1k; R_0603_1608Metric; MPN 0603WAF1001T5E; LCSC C21190
R6, R14, R15: 4.7k; R_0603_1608Metric; MPN 0603WAF4701T5E; LCSC C23162
R7, R10, R19, R23: 10k; R_0603_1608Metric; MPN 0603WAF1002T5E; LCSC C25804
R8: 47k; R_0603_1608Metric; MPN 0603WAF4702T5E; LCSC C25819
R9: 12k; R_0603_1608Metric; MPN 0603WAF1202T5E; LCSC C22790
R18: 10; R_0603_1608Metric; MPN 0603WAF100JT5E; LCSC C22859
R24, R25: 1M; R_0603_1608Metric; MPN 0603WAF1004T5E; LCSC C22935
SW1: POWER (SK-12E12-G5); SW_Slide_SPDT_Angled_HRO_SK-12E12-G5; MPN HRO SK-12E12-G5; LCSC C136720
SW3: SIQ-02FVS3; Mitsumi_SIQ-02FVS3; MPN Mitsumi SIQ-02FVS3; LCSC C2925423
U1: TP4056; SOIC-8-1EP_3.9x4.9mm_P1.27mm_EP2.41x3.3mm; MPN TP4056-42-ESOP8; LCSC C16581
U2: DW01A; SOT-23-6; MPN DW01A (PUOLOP); LCSC C351410
U3: ATmega328PB-AU; TQFP-32_7x7mm_P0.8mm; MPN ATMEGA328PB-AU; LCSC C132230
U4: RRD-102V2.0 (RDA5807M); RRD-102_RDA5807M_Module; MPN RRD-102V2.0 RDA5807M module
U5, U6: XC6206P332MR; SOT-23-3; MPN XC6206P332MR-G; LCSC C5446
U7: CH340K; SSOP-10-1EP_3.9x4.9mm_P1mm_EP2.1x3.3mm; MPN WCH CH340K; LCSC C968586
U8: USBLC6-2SC6; SOT-23-6; MPN ST USBLC6-2SC6; LCSC C7519

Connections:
+3V3: C7.1, C13.1, C18.1, J3.2, R10.1, R19.1, U3.4 (VCC), U3.6 (PE1), U3.18 (AVCC), U6.2 (VO)
+3V3R: C5.1, R14.1, R15.1, R18.1, U5.2 (VO)
AREF: C14.1, U3.20 (AREF)
BATN: BT1.2 (-), C3.2, Q1.1 (S1), Q3.2 (S), U2.6 (GND)
BAT_ADC: C6.1, R8.2, R9.1, U3.23 (PC0)
BAT_P: BT1.1 (+), Q2.3 (D), R23.1
BTN_SENSE: R6.2, R7.1, U3.24 (PC1)
CC1: J1.A5 (CC1), R1.1
CC2: J1.B5 (CC2), R2.1
CHRG_SENSE: D7.2 (A), U3.25 (PC2)
CH_RX: R20.2, U7.9 (RXD)
CH_V3: C16.1, U7.10 (V3)
CS: R5.1, U2.2 (CS)
DTR_N: C19.1, U7.4 (~DTR)
DW_VCC: C3.1, R4.2, U2.5 (VCC)
ENC_A: SW3.A, U3.32 (PD2)
ENC_B: SW3.B, U3.1 (PD3)
FM_ANT: C12.2, U4.5 (FM_ANT)
FM_L: C10.1, U4.3 (LOUT)
FM_R: C11.1, U4.2 (ROUT)
FM_SCL: R17.2, U4.7 (SCL)
FM_SDA: R16.2, U4.6 (SDA)
FM_VDD: C8.1, C9.1, R18.2, U4.10 (VDD)
GND: C1.2, C2.2, C4.2, C5.2, C6.2, C7.2, C8.2, C9.2, C13.2, C14.2, C15.2, C16.2, C17.2, C18.2, D1.1 (K), D5.1 (K), D6.1 (K), FB3.2, J1.A1 (GND), J1.A12 (GND), J1.B1 (GND), J1.B12 (GND), J1.S1 (SHIELD), J3.6, Q1.3 (S2), R1.2, R2.2, R3.2, R5.2, R7.2, R9.2, SW3.C, U1.1 (TEMP), U1.3 (GND), U1.9 (EPAD), U3.3 (PE0), U3.5 (GND), U3.21 (GND), U4.1 (GND), U5.1 (GND), U6.1 (GND), U7.3 (GND), U7.11 (GND), U8.2 (GND)
HPL_C: C10.2, FB1.1
HPR_C: C11.2, FB2.1
HP_GND: C12.1, FB3.1, J2.R2, J2.S
HP_L: FB1.2, J2.T
HP_R: FB2.2, J2.R1
LEDCHG_A: D3.2 (A), R21.2
LEDSTB_A: D4.2 (A), R22.2
LVL1: R11.1, U3.9 (PD5)
LVL1_A: D1.2 (A), R11.2
LVL2: R12.1, U3.10 (PD6)
LVL2_A: D5.2 (A), R12.2
LVL3: R13.1, U3.13 (PB1)
LVL3_A: D6.2 (A), R13.2
MCU_RX: R19.2, U3.30 (PD0), U7.8 (TXD)
MCU_TX: R20.1, U3.31 (PD1)
MISO: J3.1, U3.16 (PB4)
MOSI: J3.4, U3.15 (PB3)
OC: Q1.4 (G2), U2.3 (OC)
OD: Q1.6 (G1), U2.1 (OD)
PROG: R3.1, U1.2 (PROG)
Q2_G: Q2.1 (G), Q3.3 (D), R24.2
Q3_G: Q3.1 (G), R23.2
Q_D: Q1.2 (D12), Q1.5 (D12)
SCK: J3.3, U3.17 (PB5)
SCL: R15.2, R17.1, U3.28 (PC5)
SDA: R14.2, R16.1, U3.27 (PC4)
USB_DN: J1.A7 (D-), J1.B7 (D-), U7.2 (UD-), U8.3 (I/O2), U8.4 (I/O2)
USB_DP: J1.A6 (D+), J1.B6 (D+), U7.1 (UD+), U8.1 (I/O1), U8.6 (I/O1)
VBAT: C2.1, Q2.2 (S), Q4.2 (S), R4.1, R24.1, R25.1, SW1.2 (B), U1.5 (BAT)
VBTN: D2.2 (A), D10.2 (A), Q4.3 (D), R6.1
VBUS: C1.1, C15.1, D9.2 (A), J1.A4 (VBUS), J1.A9 (VBUS), J1.B4 (VBUS), J1.B9 (VBUS), R21.1, R22.1, U1.4 (V_{CC}), U1.8 (CE), U7.7 (VCC), U8.5 (VBUS)
VMCU: C17.1, D8.1 (K), D9.1 (K), D10.1 (K), U6.3 (VI)
VSYS: C4.1, D2.1 (K), D8.2 (A), R8.1, SW1.3 (C), U5.3 (VI)
WHEEL_SW_N: Q4.1 (G), R25.2, SW3.S
nCHRG: D3.1 (K), D7.1 (K), U1.7 (~CHRG)
nRESET: C19.2, J3.5, R10.2, U3.29 (~RESET/PC6)
nSTDBY: D4.1 (K), U1.6 (~STDBY)

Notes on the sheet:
USB-C input (power + USB 2.0 data, CC 5.1k pull-downs)
TP4056 Li-ion charger (~900 mA) + charge LEDs
18650 + reverse-polarity FETs (Q2/Q3) + DW01A / FS8205A protection
Power switch, wheel-press power FET (Q4), radio 3.3 V LDO (+3V3R), battery ADC
ATmega328PB MCU (internal 8 MHz) + AVR ISP pogo pads
Battery level bar (3x LED) + thumbwheel encoder
RRD-102 (RDA5807M) FM module, headphone out, headphone-ground antenna
USB serial: CH340K (VBUS only) + ESD + auto-reset; MCU-only 3.3 V rail
Power flags (ERC)

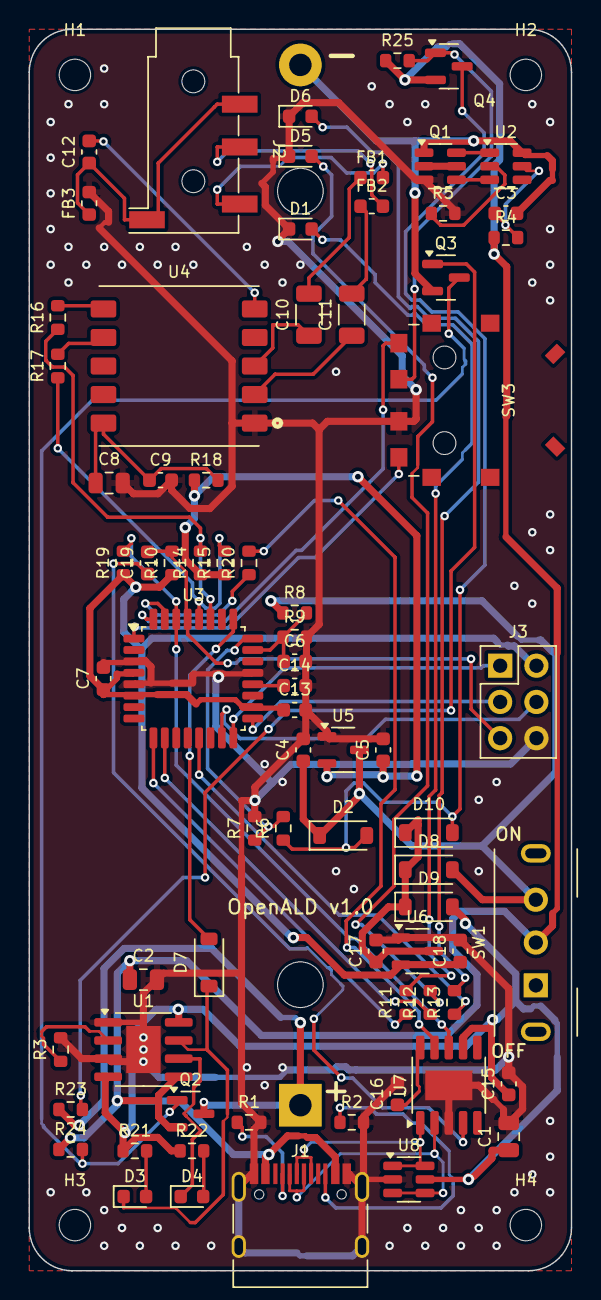
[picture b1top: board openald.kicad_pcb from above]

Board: 2 copper layers, 38.0 x 87.0 mm, 79 parts (1 on the bottom side), 61 nets.

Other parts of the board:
H1, H2, H3, H4: M2; MountingHole_2.2mm_M2

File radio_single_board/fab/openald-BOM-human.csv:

Designator(s),Qty/board,Value / description,Manufacturer part,LCSC #,JLC library,LCSC stock (live),Unit price USD (qty 10),Assembly,Link
J1,1,USB-C (power + USB 2.0 data) (USB_C_Receptacle_HRO_TYPE-C-31-M-12),HRO TYPE-C-31-M-12,C165948,Extended,281632,0.1868,JLCPCB SMT,https://www.lcsc.com/product-detail/C165948.html
"R1,R2",2,5.1k (R_0603_1608Metric),0603WAF5101T5E,C23186,Basic,19705142,0.0015,JLCPCB SMT,https://www.lcsc.com/product-detail/C23186.html
"C1,C2",2,10uF 25V (C_0805_2012Metric),CL21A106KAYNNNE,C15850,Basic,8635577,0.0315,JLCPCB SMT,https://www.lcsc.com/product-detail/C15850.html
U1,1,TP4056 (SOIC-8-1EP_3.9x4.9mm_P1.27mm_EP2.41x3.3mm),TP4056-42-ESOP8,C16581,Preferred ext.,89499,0.1852,JLCPCB SMT,https://www.lcsc.com/product-detail/C16581.html
R3,1,1.2k (R_0603_1608Metric),0603WAF1201T5E,C22765,Basic,2122275,0.0034,JLCPCB SMT,https://www.lcsc.com/product-detail/C22765.html
"R5,R11,R12,R13,R16,R17,R20,R21,R22",9,1k (R_0603_1608Metric),0603WAF1001T5E,C21190,Basic,25689733,0.0017,JLCPCB SMT,https://www.lcsc.com/product-detail/C21190.html
D3,1,Red (charging) (LED_0603_1608Metric),KT-0603R,C2286,Basic,6046029,0.0077,JLCPCB SMT,https://www.lcsc.com/product-detail/C2286.html
"D1,D4,D5,D6",4,Green (charged) / Green (level bar) (LED_0603_1608Metric),KT-0603G,C12624,Extended,296191,0.0119,JLCPCB SMT,https://www.lcsc.com/product-detail/C12624.html
"Q2,Q4",2,AO3401A (SOT-23),AOS AO3401A,C15127,Basic,1606758,0.0813,JLCPCB SMT,https://www.lcsc.com/product-detail/C15127.html
Q3,1,AO3400A (SOT-23),AOS AO3400A,C20917,Basic,916553,0.0802,JLCPCB SMT,https://www.lcsc.com/product-detail/C20917.html
"R7,R10,R19,R23",4,10k (R_0603_1608Metric),0603WAF1002T5E,C25804,Basic,43282059,0.0022,JLCPCB SMT,https://www.lcsc.com/product-detail/C25804.html
"R24,R25",2,1M (R_0603_1608Metric),0603WAF1004T5E,C22935,Basic,3921133,0.0018,JLCPCB SMT,https://www.lcsc.com/product-detail/C22935.html
U2,1,DW01A (SOT-23-6),DW01A (PUOLOP),C351410,Extended,92420,0.0532,JLCPCB SMT,https://www.lcsc.com/product-detail/C351410.html
Q1,1,FS8205A (SOT-23-6),FS8205A (TECH PUBLIC),C2830320,Extended,185458,0.0499,JLCPCB SMT,https://www.lcsc.com/product-detail/C2830320.html
R4,1,100 (R_0603_1608Metric),0603WAF1000T5E,C22775,Basic,9994733,0.002,JLCPCB SMT,https://www.lcsc.com/product-detail/C22775.html
"C3,C6,C7,C9,C13,C14,C15,C16,C19",9,100nF (C_0603_1608Metric),CC0603KRX7R9BB104,C14663,Basic,37482941,0.006,JLCPCB SMT,https://www.lcsc.com/product-detail/C14663.html
SW1,1,POWER (SK-12E12-G5) (SW_Slide_SPDT_Angled_HRO_SK-12E12-G5),HRO SK-12E12-G5,C136720,Extended,15487,0.1132,JLCPCB THT (Standard PCBA) - or delete the BOM line and hand-solder,https://www.lcsc.com/product-detail/C136720.html
"D2,D7,D8,D9,D10",5,B5819W (D_SOD-123),B5819W SL,C8598,Basic,377359,0.0262,JLCPCB SMT,https://www.lcsc.com/product-detail/C8598.html
"R6,R14,R15",3,4.7k (R_0603_1608Metric),0603WAF4701T5E,C23162,Basic,14768971,0.0028,JLCPCB SMT,https://www.lcsc.com/product-detail/C23162.html
"U5,U6",2,XC6206P332MR (SOT-23-3),XC6206P332MR-G,C5446,Basic,479522,0.1262,JLCPCB SMT,https://www.lcsc.com/product-detail/C5446.html
"C4,C17",2,1uF (C_0603_1608Metric),CL10A105KB8NNNC,C15849,Basic,12249102,0.0113,JLCPCB SMT,https://www.lcsc.com/product-detail/C15849.html
"C5,C18",2,10uF (C_0603_1608Metric),CL10A106KP8NNNC,C19702,Basic,9405851,0.0233,JLCPCB SMT,https://www.lcsc.com/product-detail/C19702.html
R8,1,47k (R_0603_1608Metric),0603WAF4702T5E,C25819,Basic,2902592,0.0016,JLCPCB SMT,https://www.lcsc.com/product-detail/C25819.html
R9,1,12k (R_0603_1608Metric),0603WAF1202T5E,C22790,Basic,1062704,0.0031,JLCPCB SMT,https://www.lcsc.com/product-detail/C22790.html
U3,1,ATmega328PB-AU (TQFP-32_7x7mm_P0.8mm),ATMEGA328PB-AU,C132230,Extended,565,1.5882,JLCPCB SMT,https://www.lcsc.com/product-detail/C132230.html
U8,1,USBLC6-2SC6 (SOT-23-6),ST USBLC6-2SC6,C7519,Extended,22712,0.1559,JLCPCB SMT,https://www.lcsc.com/product-detail/C7519.html
U7,1,CH340K (SSOP-10-1EP_3.9x4.9mm_P1mm_EP2.1x3.3mm),WCH CH340K,C968586,Extended,30951,0.5464,JLCPCB SMT,https://www.lcsc.com/product-detail/C968586.html
SW3,1,SIQ-02FVS3 (Mitsumi_SIQ-02FVS3),Mitsumi SIQ-02FVS3,C2925423,Extended,1290,3.0374,JLCPCB SMT,https://www.lcsc.com/product-detail/C2925423.html
R18,1,10 (R_0603_1608Metric),0603WAF100JT5E,C22859,Basic,5524270,0.002,JLCPCB SMT,https://www.lcsc.com/product-detail/C22859.html
C8,1,22uF (C_0805_2012Metric),CL21A226MAQNNNE,C45783,Basic,4143825,0.1055,JLCPCB SMT,https://www.lcsc.com/product-detail/C45783.html
"C10,C11",2,100uF 6.3V (C_1206_3216Metric),CL31A107MQHNNNE,C15008,Basic,1561175,0.109,JLCPCB SMT,https://www.lcsc.com/product-detail/C15008.html
"FB1,FB2,FB3",3,600R@100MHz (L_0603_1608Metric),GZ1608D601TF,C1002,Basic,403719,0.0115,JLCPCB SMT,https://www.lcsc.com/product-detail/C1002.html
C12,1,1nF (C_0603_1608Metric),CL10B102KB8NNNC,C1588,Basic,5973452,0.0082,JLCPCB SMT,https://www.lcsc.com/product-detail/C1588.html
J2,1,3.5mm jack PJ-320D-4A (Jack_3.5mm_KoreanHropartsElec_PJ-320D-4A_Horizontal),HRO PJ-320D-4A,C95562,Extended,973,0.1216,JLCPCB SMT,https://www.lcsc.com/product-detail/C95562.html
U4,1,RRD-102V2.0 RDA5807M FM module (11x11mm castellated),RRD-102V2.0 RDA5807M module,,—,—,~$1-2 ea (often sold in 5-10 packs),Hand solder,https://www.amazon.com/s?k=RDA5807M+RRD-102+FM+module
BT1,1,"MPD BH-18650-PC 18650 PCB holder (THT, 2 pins 72.9mm)",MPD BH-18650-PC,,—,—,~$3,Hand solder,https://www.digikey.com/en/products/result?keywords=BH-18650-PC
J3,1,"2x3 2.54mm AVR-ISP pogo pads (ATmega328PB MISO/SCK/MOSI/RESET, 3.3 V) - bootloader burn only; do not leave a header fitted",2x3 2.54mm header / pogo (DNP),,—,—,~$0.10 (or a 2x3 pogo clip),DNP,https://www.digikey.com/en/products/result?keywords=2x3%20pi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
—,1,18650 Li-ion cell (flat or button top; protected cells up to ~69mm fit the MPD holder),,,,,~$5,Off-board,https://www.amazon.com/s?k=18650+battery
—,4,"M2 x 12 mm screws, pan or socket head (M2 x 16 if using the hex-nut case option)",,,,,~$0.05,Off-board,https://www.amazon.com/s?k=M2+x+12mm+socket+head+screws
—,4,"M2 brass heat-set inserts, OD 3.2-3.5 mm x L 3-4 mm (or M2 hex nuts)",,,,,~$0.05,Off-board,https://www.amazon.com/s?k=M2+heat+set+inserts
